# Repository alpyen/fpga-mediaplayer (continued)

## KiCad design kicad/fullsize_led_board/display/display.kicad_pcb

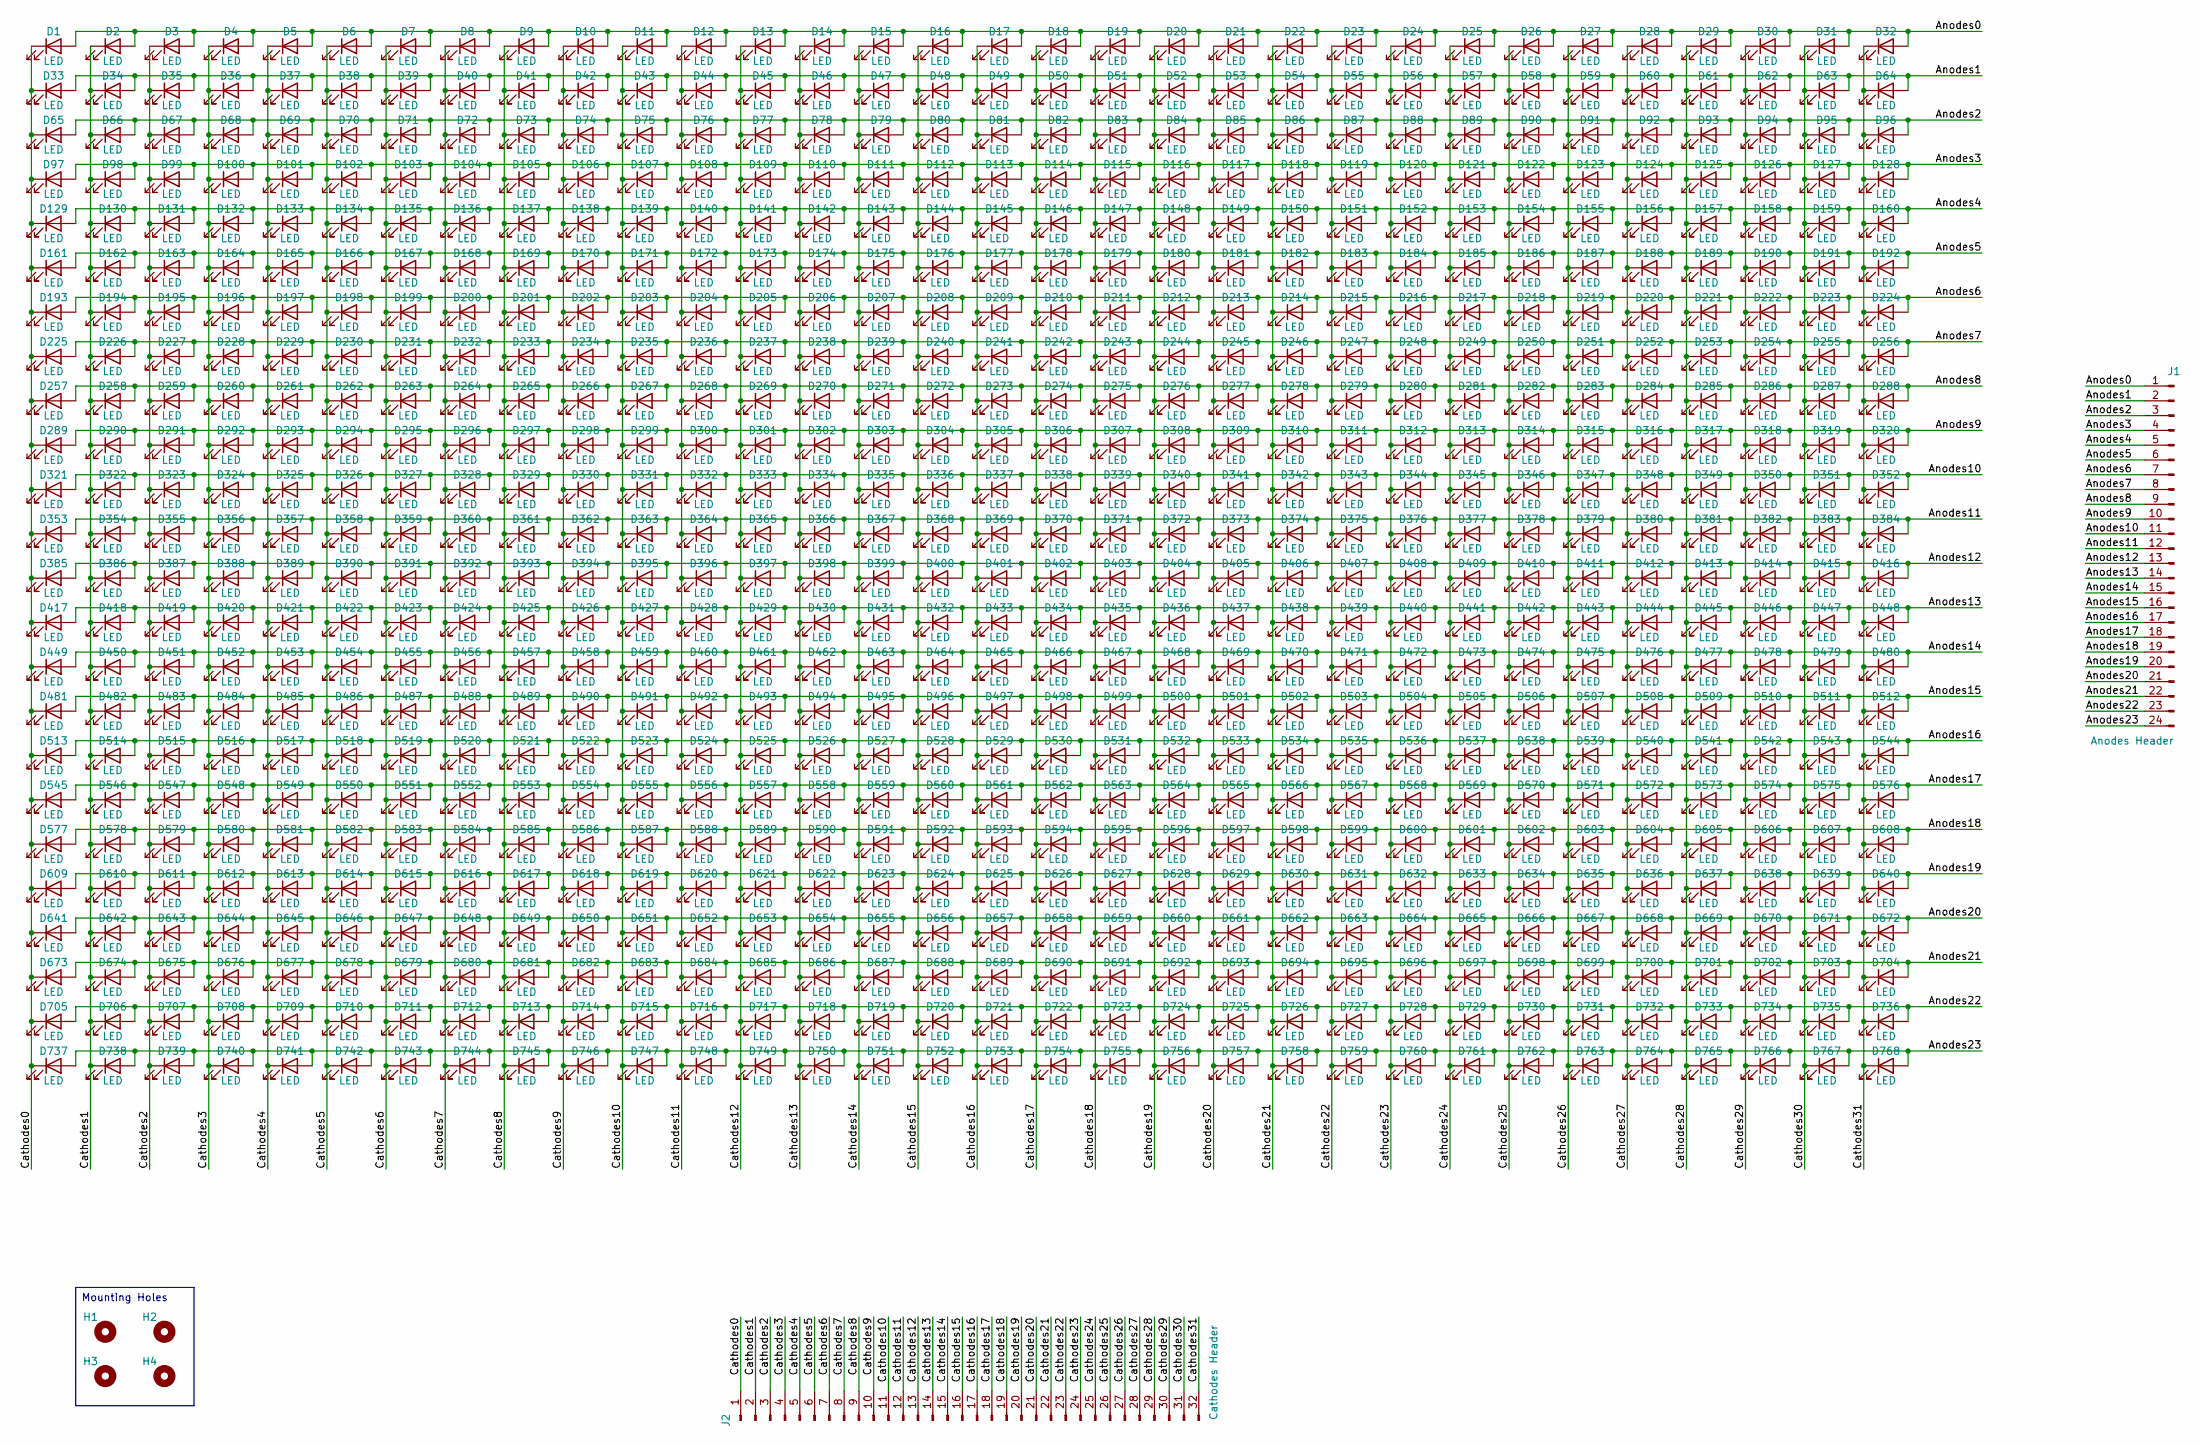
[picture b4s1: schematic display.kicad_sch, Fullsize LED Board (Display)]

Parts:
D1, D2, D3, D4, D5, D6, D7, D8, D9, D10, D11, D12, D13, D14, D15, D16, D17, D18, D19, D20, D21, D22, D23, D24, D25, D26, D27, D28, D29, D30, D31, D32, D33, D34, D35, D36, D37, D38, D39, D40, D41, D42, D43, D44, D45, D46, D47, D48, D49, D50, D51, D52, D53, D54, D55, D56, D57, D58, D59, D60, D61, D62, D63, D64, D65, D66, D67, D68, D69, D70, D71, D72, D73, D74, D75, D76, D77, D78, D79, D80, D81, D82, D83, D84, D85, D86, D87, D88, D89, D90, D91, D92, D93, D94, D95, D96, D97, D98, D99, D100, D101, D102, D103, D104, D105, D106, D107, D108, D109, D110, D111, D112, D113, D114, D115, D116, D117, D118, D119, D120, D121, D122, D123, D124, D125, D126, D127, D128, D129, D130, D131, D132, D133, D134, D135, D136, D137, D138, D139, D140, D141, D142, D143, D144, D145, D146, D147, D148, D149, D150, D151, D152, D153, D154, D155, D156, D157, D158, D159, D160, D161, D162, D163, D164, D165, D166, D167, D168, D169, D170, D171, D172, D173, D174, D175, D176, D177, D178, D179, D180, D181, D182, D183, D184, D185, D186, D187, D188, D189, D190, D191, D192, D193, D194, D195, D196, D197, D198, D199, D200, D201, D202, D203, D204, D205, D206, D207, D208, D209, D210, D211, D212, D213, D214, D215, D216, D217, D218, D219, D220, D221, D222, D223, D224, D225, D226, D227, D228, D229, D230, D231, D232, D233, D234, D235, D236, D237, D238, D239, D240, D241, D242, D243, D244, D245, D246, D247, D248, D249, D250, D251, D252, D253, D254, D255, D256, D257, D258, D259, D260, D261, D262, D263, D264, D265, D266, D267, D268, D269, D270, D271, D272, D273, D274, D275, D276, D277, D278, D279, D280, D281, D282, D283, D284, D285, D286, D287, D288, D289, D290, D291, D292, D293, D294, D295, D296, D297, D298, D299, D300, D301, D302, D303, D304, D305, D306, D307, D308, D309, D310, D311, D312, D313, D314, D315, D316, D317, D318, D319, D320, D321, D322, D323, D324, D325, D326, D327, D328, D329, D330, D331, D332, D333, D334, D335, D336, D337, D338, D339, D340, D341, D342, D343, D344, D345, D346, D347, D348, D349, D350, D351, D352, D353, D354, D355, D356, D357, D358, D359, D360, D361, D362, D363, D364, D365, D366, D367, D368, D369, D370, D371, D372, D373, D374, D375, D376, D377, D378, D379, D380, D381, D382, D383, D384, D385, D386, D387, D388, D389, D390, D391, D392, D393, D394, D395, D396, D397, D398, D399, D400, D401, D402, D403, D404, D405, D406, D407, D408, D409, D410, D411, D412, D413, D414, D415, D416, D417, D418, D419, D420, D421, D422, D423, D424, D425, D426, D427, D428, D429, D430, D431, D432, D433, D434, D435, D436, D437, D438, D439, D440, D441, D442, D443, D444, D445, D446, D447, D448, D449, D450, D451, D452, D453, D454, D455, D456, D457, D458, D459, D460, D461, D462, D463, D464, D465, D466, D467, D468, D469, D470, D471, D472, D473, D474, D475, D476, D477, D478, D479, D480, D481, D482, D483, D484, D485, D486, D487, D488, D489, D490, D491, D492, D493, D494, D495, D496, D497, D498, D499, D500, D501, D502, D503, D504, D505, D506, D507, D508, D509, D510, D511, D512, D513, D514, D515, D516, D517, D518, D519, D520, D521, D522, D523, D524, D525, D526, D527, D528, D529, D530, D531, D532, D533, D534, D535, D536, D537, D538, D539, D540, D541, D542, D543, D544, D545, D546, D547, D548, D549, D550, D551, D552, D553, D554, D555, D556, D557, D558, D559, D560, D561, D562, D563, D564, D565, D566, D567, D568, D569, D570, D571, D572, D573, D574, D575, D576, D577, D578, D579, D580, D581, D582, D583, D584, D585, D586, D587, D588, D589, D590, D591, D592, D593, D594, D595, D596, D597, D598, D599, D600, D601, D602, D603, D604, D605, D606, D607, D608, D609, D610, D611, D612, D613, D614, D615, D616, D617, D618, D619, D620, D621, D622, D623, D624, D625, D626, D627, D628, D629, D630, D631, D632, D633, D634, D635, D636, D637, D638, D639, D640, D641, D642, D643, D644, D645, D646, D647, D648, D649, D650, D651, D652, D653, D654, D655, D656, D657, D658, D659, D660, D661, D662, D663, D664, D665, D666, D667, D668, D669, D670, D671, D672, D673, D674, D675, D676, D677, D678, D679, D680, D681, D682, D683, D684, D685, D686, D687, D688, D689, D690, D691, D692, D693, D694, D695, D696, D697, D698, D699, D700, D701, D702, D703, D704, D705, D706, D707, D708, D709, D710, D711, D712, D713, D714, D715, D716, D717, D718, D719, D720, D721, D722, D723, D724, D725, D726, D727, D728, D729, D730, D731, D732, D733, D734, D735, D736, D737, D738, D739, D740, D741, D742, D743, D744, D745, D746, D747, D748, D749, D750, D751, D752, D753, D754, D755, D756, D757, D758, D759, D760, D761, D762, D763, D764, D765, D766, D767, D768: LED; LED_D5.0mm
H1, H2, H3, H4: MountingHole_3mm
J1: Anodes Header; PinHeader_1x24_P2.54mm_Vertical
J2: Cathodes Header; PinHeader_1x32_P2.54mm_Vertical

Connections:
/Anodes0: D1.2 (A), D2.2 (A), D3.2 (A), D4.2 (A), D5.2 (A), D6.2 (A), D7.2 (A), D8.2 (A), D9.2 (A), D10.2 (A), D11.2 (A), D12.2 (A), D13.2 (A), D14.2 (A), D15.2 (A), D16.2 (A), D17.2 (A), D18.2 (A), D19.2 (A), D20.2 (A), D21.2 (A), D22.2 (A), D23.2 (A), D24.2 (A), D25.2 (A), D26.2 (A), D27.2 (A), D28.2 (A), D29.2 (A), D30.2 (A), D31.2 (A), D32.2 (A), J1.1
/Anodes1: D33.2 (A), D34.2 (A), D35.2 (A), D36.2 (A), D37.2 (A), D38.2 (A), D39.2 (A), D40.2 (A), D41.2 (A), D42.2 (A), D43.2 (A), D44.2 (A), D45.2 (A), D46.2 (A), D47.2 (A), D48.2 (A), D49.2 (A), D50.2 (A), D51.2 (A), D52.2 (A), D53.2 (A), D54.2 (A), D55.2 (A), D56.2 (A), D57.2 (A), D58.2 (A), D59.2 (A), D60.2 (A), D61.2 (A), D62.2 (A), D63.2 (A), D64.2 (A), J1.2
/Anodes2: D65.2 (A), D66.2 (A), D67.2 (A), D68.2 (A), D69.2 (A), D70.2 (A), D71.2 (A), D72.2 (A), D73.2 (A), D74.2 (A), D75.2 (A), D76.2 (A), D77.2 (A), D78.2 (A), D79.2 (A), D80.2 (A), D81.2 (A), D82.2 (A), D83.2 (A), D84.2 (A), D85.2 (A), D86.2 (A), D87.2 (A), D88.2 (A), D89.2 (A), D90.2 (A), D91.2 (A), D92.2 (A), D93.2 (A), D94.2 (A), D95.2 (A), D96.2 (A), J1.3
/Anodes3: D97.2 (A), D98.2 (A), D99.2 (A), D100.2 (A), D101.2 (A), D102.2 (A), D103.2 (A), D104.2 (A), D105.2 (A), D106.2 (A), D107.2 (A), D108.2 (A), D109.2 (A), D110.2 (A), D111.2 (A), D112.2 (A), D113.2 (A), D114.2 (A), D115.2 (A), D116.2 (A), D117.2 (A), D118.2 (A), D119.2 (A), D120.2 (A), D121.2 (A), D122.2 (A), D123.2 (A), D124.2 (A), D125.2 (A), D126.2 (A), D127.2 (A), D128.2 (A), J1.4
/Anodes4: D129.2 (A), D130.2 (A), D131.2 (A), D132.2 (A), D133.2 (A), D134.2 (A), D135.2 (A), D136.2 (A), D137.2 (A), D138.2 (A), D139.2 (A), D140.2 (A), D141.2 (A), D142.2 (A), D143.2 (A), D144.2 (A), D145.2 (A), D146.2 (A), D147.2 (A), D148.2 (A), D149.2 (A), D150.2 (A), D151.2 (A), D152.2 (A), D153.2 (A), D154.2 (A), D155.2 (A), D156.2 (A), D157.2 (A), D158.2 (A), D159.2 (A), D160.2 (A), J1.5
/Anodes5: D161.2 (A), D162.2 (A), D163.2 (A), D164.2 (A), D165.2 (A), D166.2 (A), D167.2 (A), D168.2 (A), D169.2 (A), D170.2 (A), D171.2 (A), D172.2 (A), D173.2 (A), D174.2 (A), D175.2 (A), D176.2 (A), D177.2 (A), D178.2 (A), D179.2 (A), D180.2 (A), D181.2 (A), D182.2 (A), D183.2 (A), D184.2 (A), D185.2 (A), D186.2 (A), D187.2 (A), D188.2 (A), D189.2 (A), D190.2 (A), D191.2 (A), D192.2 (A), J1.6
/Anodes6: D193.2 (A), D194.2 (A), D195.2 (A), D196.2 (A), D197.2 (A), D198.2 (A), D199.2 (A), D200.2 (A), D201.2 (A), D202.2 (A), D203.2 (A), D204.2 (A), D205.2 (A), D206.2 (A), D207.2 (A), D208.2 (A), D209.2 (A), D210.2 (A), D211.2 (A), D212.2 (A), D213.2 (A), D214.2 (A), D215.2 (A), D216.2 (A), D217.2 (A), D218.2 (A), D219.2 (A), D220.2 (A), D221.2 (A), D222.2 (A), D223.2 (A), D224.2 (A), J1.7
/Anodes7: D225.2 (A), D226.2 (A), D227.2 (A), D228.2 (A), D229.2 (A), D230.2 (A), D231.2 (A), D232.2 (A), D233.2 (A), D234.2 (A), D235.2 (A), D236.2 (A), D237.2 (A), D238.2 (A), D239.2 (A), D240.2 (A), D241.2 (A), D242.2 (A), D243.2 (A), D244.2 (A), D245.2 (A), D246.2 (A), D247.2 (A), D248.2 (A), D249.2 (A), D250.2 (A), D251.2 (A), D252.2 (A), D253.2 (A), D254.2 (A), D255.2 (A), D256.2 (A), J1.8
/Anodes8: D257.2 (A), D258.2 (A), D259.2 (A), D260.2 (A), D261.2 (A), D262.2 (A), D263.2 (A), D264.2 (A), D265.2 (A), D266.2 (A), D267.2 (A), D268.2 (A), D269.2 (A), D270.2 (A), D271.2 (A), D272.2 (A), D273.2 (A), D274.2 (A), D275.2 (A), D276.2 (A), D277.2 (A), D278.2 (A), D279.2 (A), D280.2 (A), D281.2 (A), D282.2 (A), D283.2 (A), D284.2 (A), D285.2 (A), D286.2 (A), D287.2 (A), D288.2 (A), J1.9
/Anodes9: D289.2 (A), D290.2 (A), D291.2 (A), D292.2 (A), D293.2 (A), D294.2 (A), D295.2 (A), D296.2 (A), D297.2 (A), D298.2 (A), D299.2 (A), D300.2 (A), D301.2 (A), D302.2 (A), D303.2 (A), D304.2 (A), D305.2 (A), D306.2 (A), D307.2 (A), D308.2 (A), D309.2 (A), D310.2 (A), D311.2 (A), D312.2 (A), D313.2 (A), D314.2 (A), D315.2 (A), D316.2 (A), D317.2 (A), D318.2 (A), D319.2 (A), D320.2 (A), J1.10
/Anodes10: D321.2 (A), D322.2 (A), D323.2 (A), D324.2 (A), D325.2 (A), D326.2 (A), D327.2 (A), D328.2 (A), D329.2 (A), D330.2 (A), D331.2 (A), D332.2 (A), D333.2 (A), D334.2 (A), D335.2 (A), D336.2 (A), D337.2 (A), D338.2 (A), D339.2 (A), D340.2 (A), D341.2 (A), D342.2 (A), D343.2 (A), D344.2 (A), D345.2 (A), D346.2 (A), D347.2 (A), D348.2 (A), D349.2 (A), D350.2 (A), D351.2 (A), D352.2 (A), J1.11
/Anodes11: D353.2 (A), D354.2 (A), D355.2 (A), D356.2 (A), D357.2 (A), D358.2 (A), D359.2 (A), D360.2 (A), D361.2 (A), D362.2 (A), D363.2 (A), D364.2 (A), D365.2 (A), D366.2 (A), D367.2 (A), D368.2 (A), D369.2 (A), D370.2 (A), D371.2 (A), D372.2 (A), D373.2 (A), D374.2 (A), D375.2 (A), D376.2 (A), D377.2 (A), D378.2 (A), D379.2 (A), D380.2 (A), D381.2 (A), D382.2 (A), D383.2 (A), D384.2 (A), J1.12
/Anodes12: D385.2 (A), D386.2 (A), D387.2 (A), D388.2 (A), D389.2 (A), D390.2 (A), D391.2 (A), D392.2 (A), D393.2 (A), D394.2 (A), D395.2 (A), D396.2 (A), D397.2 (A), D398.2 (A), D399.2 (A), D400.2 (A), D401.2 (A), D402.2 (A), D403.2 (A), D404.2 (A), D405.2 (A), D406.2 (A), D407.2 (A), D408.2 (A), D409.2 (A), D410.2 (A), D411.2 (A), D412.2 (A), D413.2 (A), D414.2 (A), D415.2 (A), D416.2 (A), J1.13
/Anodes13: D417.2 (A), D418.2 (A), D419.2 (A), D420.2 (A), D421.2 (A), D422.2 (A), D423.2 (A), D424.2 (A), D425.2 (A), D426.2 (A), D427.2 (A), D428.2 (A), D429.2 (A), D430.2 (A), D431.2 (A), D432.2 (A), D433.2 (A), D434.2 (A), D435.2 (A), D436.2 (A), D437.2 (A), D438.2 (A), D439.2 (A), D440.2 (A), D441.2 (A), D442.2 (A), D443.2 (A), D444.2 (A), D445.2 (A), D446.2 (A), D447.2 (A), D448.2 (A), J1.14
/Anodes14: D449.2 (A), D450.2 (A), D451.2 (A), D452.2 (A), D453.2 (A), D454.2 (A), D455.2 (A), D456.2 (A), D457.2 (A), D458.2 (A), D459.2 (A), D460.2 (A), D461.2 (A), D462.2 (A), D463.2 (A), D464.2 (A), D465.2 (A), D466.2 (A), D467.2 (A), D468.2 (A), D469.2 (A), D470.2 (A), D471.2 (A), D472.2 (A), D473.2 (A), D474.2 (A), D475.2 (A), D476.2 (A), D477.2 (A), D478.2 (A), D479.2 (A), D480.2 (A), J1.15
/Anodes15: D481.2 (A), D482.2 (A), D483.2 (A), D484.2 (A), D485.2 (A), D486.2 (A), D487.2 (A), D488.2 (A), D489.2 (A), D490.2 (A), D491.2 (A), D492.2 (A), D493.2 (A), D494.2 (A), D495.2 (A), D496.2 (A), D497.2 (A), D498.2 (A), D499.2 (A), D500.2 (A), D501.2 (A), D502.2 (A), D503.2 (A), D504.2 (A), D505.2 (A), D506.2 (A), D507.2 (A), D508.2 (A), D509.2 (A), D510.2 (A), D511.2 (A), D512.2 (A), J1.16
/Anodes16: D513.2 (A), D514.2 (A), D515.2 (A), D516.2 (A), D517.2 (A), D518.2 (A), D519.2 (A), D520.2 (A), D521.2 (A), D522.2 (A), D523.2 (A), D524.2 (A), D525.2 (A), D526.2 (A), D527.2 (A), D528.2 (A), D529.2 (A), D530.2 (A), D531.2 (A), D532.2 (A), D533.2 (A), D534.2 (A), D535.2 (A), D536.2 (A), D537.2 (A), D538.2 (A), D539.2 (A), D540.2 (A), D541.2 (A), D542.2 (A), D543.2 (A), D544.2 (A), J1.17
/Anodes17: D545.2 (A), D546.2 (A), D547.2 (A), D548.2 (A), D549.2 (A), D550.2 (A), D551.2 (A), D552.2 (A), D553.2 (A), D554.2 (A), D555.2 (A), D556.2 (A), D557.2 (A), D558.2 (A), D559.2 (A), D560.2 (A), D561.2 (A), D562.2 (A), D563.2 (A), D564.2 (A), D565.2 (A), D566.2 (A), D567.2 (A), D568.2 (A), D569.2 (A), D570.2 (A), D571.2 (A), D572.2 (A), D573.2 (A), D574.2 (A), D575.2 (A), D576.2 (A), J1.18
/Anodes18: D577.2 (A), D578.2 (A), D579.2 (A), D580.2 (A), D581.2 (A), D582.2 (A), D583.2 (A), D584.2 (A), D585.2 (A), D586.2 (A), D587.2 (A), D588.2 (A), D589.2 (A), D590.2 (A), D591.2 (A), D592.2 (A), D593.2 (A), D594.2 (A), D595.2 (A), D596.2 (A), D597.2 (A), D598.2 (A), D599.2 (A), D600.2 (A), D601.2 (A), D602.2 (A), D603.2 (A), D604.2 (A), D605.2 (A), D606.2 (A), D607.2 (A), D608.2 (A), J1.19
/Anodes19: D609.2 (A), D610.2 (A), D611.2 (A), D612.2 (A), D613.2 (A), D614.2 (A), D615.2 (A), D616.2 (A), D617.2 (A), D618.2 (A), D619.2 (A), D620.2 (A), D621.2 (A), D622.2 (A), D623.2 (A), D624.2 (A), D625.2 (A), D626.2 (A), D627.2 (A), D628.2 (A), D629.2 (A), D630.2 (A), D631.2 (A), D632.2 (A), D633.2 (A), D634.2 (A), D635.2 (A), D636.2 (A), D637.2 (A), D638.2 (A), D639.2 (A), D640.2 (A), J1.20
/Anodes20: D641.2 (A), D642.2 (A), D643.2 (A), D644.2 (A), D645.2 (A), D646.2 (A), D647.2 (A), D648.2 (A), D649.2 (A), D650.2 (A), D651.2 (A), D652.2 (A), D653.2 (A), D654.2 (A), D655.2 (A), D656.2 (A), D657.2 (A), D658.2 (A), D659.2 (A), D660.2 (A), D661.2 (A), D662.2 (A), D663.2 (A), D664.2 (A), D665.2 (A), D666.2 (A), D667.2 (A), D668.2 (A), D669.2 (A), D670.2 (A), D671.2 (A), D672.2 (A), J1.21
/Anodes21: D673.2 (A), D674.2 (A), D675.2 (A), D676.2 (A), D677.2 (A), D678.2 (A), D679.2 (A), D680.2 (A), D681.2 (A), D682.2 (A), D683.2 (A), D684.2 (A), D685.2 (A), D686.2 (A), D687.2 (A), D688.2 (A), D689.2 (A), D690.2 (A), D691.2 (A), D692.2 (A), D693.2 (A), D694.2 (A), D695.2 (A), D696.2 (A), D697.2 (A), D698.2 (A), D699.2 (A), D700.2 (A), D701.2 (A), D702.2 (A), D703.2 (A), D704.2 (A), J1.22
/Anodes22: D705.2 (A), D706.2 (A), D707.2 (A), D708.2 (A), D709.2 (A), D710.2 (A), D711.2 (A), D712.2 (A), D713.2 (A), D714.2 (A), D715.2 (A), D716.2 (A), D717.2 (A), D718.2 (A), D719.2 (A), D720.2 (A), D721.2 (A), D722.2 (A), D723.2 (A), D724.2 (A), D725.2 (A), D726.2 (A), D727.2 (A), D728.2 (A), D729.2 (A), D730.2 (A), D731.2 (A), D732.2 (A), D733.2 (A), D734.2 (A), D735.2 (A), D736.2 (A), J1.23
/Anodes23: D737.2 (A), D738.2 (A), D739.2 (A), D740.2 (A), D741.2 (A), D742.2 (A), D743.2 (A), D744.2 (A), D745.2 (A), D746.2 (A), D747.2 (A), D748.2 (A), D749.2 (A), D750.2 (A), D751.2 (A), D752.2 (A), D753.2 (A), D754.2 (A), D755.2 (A), D756.2 (A), D757.2 (A), D758.2 (A), D759.2 (A), D760.2 (A), D761.2 (A), D762.2 (A), D763.2 (A), D764.2 (A), D765.2 (A), D766.2 (A), D767.2 (A), D768.2 (A), J1.24
/Cathodes0: D1.1 (K), D33.1 (K), D65.1 (K), D97.1 (K), D129.1 (K), D161.1 (K), D193.1 (K), D225.1 (K), D257.1 (K), D289.1 (K), D321.1 (K), D353.1 (K), D385.1 (K), D417.1 (K), D449.1 (K), D481.1 (K), D513.1 (K), D545.1 (K), D577.1 (K), D609.1 (K), D641.1 (K), D673.1 (K), D705.1 (K), D737.1 (K), J2.1
/Cathodes1: D2.1 (K), D34.1 (K), D66.1 (K), D98.1 (K), D130.1 (K), D162.1 (K), D194.1 (K), D226.1 (K), D258.1 (K), D290.1 (K), D322.1 (K), D354.1 (K), D386.1 (K), D418.1 (K), D450.1 (K), D482.1 (K), D514.1 (K), D546.1 (K), D578.1 (K), D610.1 (K), D642.1 (K), D674.1 (K), D706.1 (K), D738.1 (K), J2.2
/Cathodes2: D3.1 (K), D35.1 (K), D67.1 (K), D99.1 (K), D131.1 (K), D163.1 (K), D195.1 (K), D227.1 (K), D259.1 (K), D291.1 (K), D323.1 (K), D355.1 (K), D387.1 (K), D419.1 (K), D451.1 (K), D483.1 (K), D515.1 (K), D547.1 (K), D579.1 (K), D611.1 (K), D643.1 (K), D675.1 (K), D707.1 (K), D739.1 (K), J2.3
/Cathodes3: D4.1 (K), D36.1 (K), D68.1 (K), D100.1 (K), D132.1 (K), D164.1 (K), D196.1 (K), D228.1 (K), D260.1 (K), D292.1 (K), D324.1 (K), D356.1 (K), D388.1 (K), D420.1 (K), D452.1 (K), D484.1 (K), D516.1 (K), D548.1 (K), D580.1 (K), D612.1 (K), D644.1 (K), D676.1 (K), D708.1 (K), D740.1 (K), J2.4
/Cathodes4: D5.1 (K), D37.1 (K), D69.1 (K), D101.1 (K), D133.1 (K), D165.1 (K), D197.1 (K), D229.1 (K), D261.1 (K), D293.1 (K), D325.1 (K), D357.1 (K), D389.1 (K), D421.1 (K), D453.1 (K), D485.1 (K), D517.1 (K), D549.1 (K), D581.1 (K), D613.1 (K), D645.1 (K), D677.1 (K), D709.1 (K), D741.1 (K), J2.5
/Cathodes5: D6.1 (K), D38.1 (K), D70.1 (K), D102.1 (K), D134.1 (K), D166.1 (K), D198.1 (K), D230.1 (K), D262.1 (K), D294.1 (K), D326.1 (K), D358.1 (K), D390.1 (K), D422.1 (K), D454.1 (K), D486.1 (K), D518.1 (K), D550.1 (K), D582.1 (K), D614.1 (K), D646.1 (K), D678.1 (K), D710.1 (K), D742.1 (K), J2.6
/Cathodes6: D7.1 (K), D39.1 (K), D71.1 (K), D103.1 (K), D135.1 (K), D167.1 (K), D199.1 (K), D231.1 (K), D263.1 (K), D295.1 (K), D327.1 (K), D359.1 (K), D391.1 (K), D423.1 (K), D455.1 (K), D487.1 (K), D519.1 (K), D551.1 (K), D583.1 (K), D615.1 (K), D647.1 (K), D679.1 (K), D711.1 (K), D743.1 (K), J2.7
/Cathodes7: D8.1 (K), D40.1 (K), D72.1 (K), D104.1 (K), D136.1 (K), D168.1 (K), D200.1 (K), D232.1 (K), D264.1 (K), D296.1 (K), D328.1 (K), D360.1 (K), D392.1 (K), D424.1 (K), D456.1 (K), D488.1 (K), D520.1 (K), D552.1 (K), D584.1 (K), D616.1 (K), D648.1 (K), D680.1 (K), D712.1 (K), D744.1 (K), J2.8
/Cathodes8: D9.1 (K), D41.1 (K), D73.1 (K), D105.1 (K), D137.1 (K), D169.1 (K), D201.1 (K), D233.1 (K), D265.1 (K), D297.1 (K), D329.1 (K), D361.1 (K), D393.1 (K), D425.1 (K), D457.1 (K), D489.1 (K), D521.1 (K), D553.1 (K), D585.1 (K), D617.1 (K), D649.1 (K), D681.1 (K), D713.1 (K), D745.1 (K), J2.9
/Cathodes9: D10.1 (K), D42.1 (K), D74.1 (K), D106.1 (K), D138.1 (K), D170.1 (K), D202.1 (K), D234.1 (K), D266.1 (K), D298.1 (K), D330.1 (K), D362.1 (K), D394.1 (K), D426.1 (K), D458.1 (K), D490.1 (K), D522.1 (K), D554.1 (K), D586.1 (K), D618.1 (K), D650.1 (K), D682.1 (K), D714.1 (K), D746.1 (K), J2.10
/Cathodes10: D11.1 (K), D43.1 (K), D75.1 (K), D107.1 (K), D139.1 (K), D171.1 (K), D203.1 (K), D235.1 (K), D267.1 (K), D299.1 (K), D331.1 (K), D363.1 (K), D395.1 (K), D427.1 (K), D459.1 (K), D491.1 (K), D523.1 (K), D555.1 (K), D587.1 (K), D619.1 (K), D651.1 (K), D683.1 (K), D715.1 (K), D747.1 (K), J2.11
/Cathodes11: D12.1 (K), D44.1 (K), D76.1 (K), D108.1 (K), D140.1 (K), D172.1 (K), D204.1 (K), D236.1 (K), D268.1 (K), D300.1 (K), D332.1 (K), D364.1 (K), D396.1 (K), D428.1 (K), D460.1 (K), D492.1 (K), D524.1 (K), D556.1 (K), D588.1 (K), D620.1 (K), D652.1 (K), D684.1 (K), D716.1 (K), D748.1 (K), J2.12
/Cathodes12: D13.1 (K), D45.1 (K), D77.1 (K), D109.1 (K), D141.1 (K), D173.1 (K), D205.1 (K), D237.1 (K), D269.1 (K), D301.1 (K), D333.1 (K), D365.1 (K), D397.1 (K), D429.1 (K), D461.1 (K), D493.1 (K), D525.1 (K), D557.1 (K), D589.1 (K), D621.1 (K), D653.1 (K), D685.1 (K), D717.1 (K), D749.1 (K), J2.13
/Cathodes13: D14.1 (K), D46.1 (K), D78.1 (K), D110.1 (K), D142.1 (K), D174.1 (K), D206.1 (K), D238.1 (K), D270.1 (K), D302.1 (K), D334.1 (K), D366.1 (K), D398.1 (K), D430.1 (K), D462.1 (K), D494.1 (K), D526.1 (K), D558.1 (K), D590.1 (K), D622.1 (K), D654.1 (K), D686.1 (K), D718.1 (K), D750.1 (K), J2.14
/Cathodes14: D15.1 (K), D47.1 (K), D79.1 (K), D111.1 (K), D143.1 (K), D175.1 (K), D207.1 (K), D239.1 (K), D271.1 (K), D303.1 (K), D335.1 (K), D367.1 (K), D399.1 (K), D431.1 (K), D463.1 (K), D495.1 (K), D527.1 (K), D559.1 (K), D591.1 (K), D623.1 (K), D655.1 (K), D687.1 (K), D719.1 (K), D751.1 (K), J2.15
/Cathodes15: D16.1 (K), D48.1 (K), D80.1 (K), D112.1 (K), D144.1 (K), D176.1 (K), D208.1 (K), D240.1 (K), D272.1 (K), D304.1 (K), D336.1 (K), D368.1 (K), D400.1 (K), D432.1 (K), D464.1 (K), D496.1 (K), D528.1 (K), D560.1 (K), D592.1 (K), D624.1 (K), D656.1 (K), D688.1 (K), D720.1 (K), D752.1 (K), J2.16
/Cathodes16: D17.1 (K), D49.1 (K), D81.1 (K), D113.1 (K), D145.1 (K), D177.1 (K), D209.1 (K), D241.1 (K), D273.1 (K), D305.1 (K), D337.1 (K), D369.1 (K), D401.1 (K), D433.1 (K), D465.1 (K), D497.1 (K), D529.1 (K), D561.1 (K), D593.1 (K), D625.1 (K), D657.1 (K), D689.1 (K), D721.1 (K), D753.1 (K), J2.17
/Cathodes17: D18.1 (K), D50.1 (K), D82.1 (K), D114.1 (K), D146.1 (K), D178.1 (K), D210.1 (K), D242.1 (K), D274.1 (K), D306.1 (K), D338.1 (K), D370.1 (K), D402.1 (K), D434.1 (K), D466.1 (K), D498.1 (K), D530.1 (K), D562.1 (K), D594.1 (K), D626.1 (K), D658.1 (K), D690.1 (K), D722.1 (K), D754.1 (K), J2.18
/Cathodes18: D19.1 (K), D51.1 (K), D83.1 (K), D115.1 (K), D147.1 (K), D179.1 (K), D211.1 (K), D243.1 (K), D275.1 (K), D307.1 (K), D339.1 (K), D371.1 (K), D403.1 (K), D435.1 (K), D467.1 (K), D499.1 (K), D531.1 (K), D563.1 (K), D595.1 (K), D627.1 (K), D659.1 (K), D691.1 (K), D723.1 (K), D755.1 (K), J2.19
/Cathodes19: D20.1 (K), D52.1 (K), D84.1 (K), D116.1 (K), D148.1 (K), D180.1 (K), D212.1 (K), D244.1 (K), D276.1 (K), D308.1 (K), D340.1 (K), D372.1 (K), D404.1 (K), D436.1 (K), D468.1 (K), D500.1 (K), D532.1 (K), D564.1 (K), D596.1 (K), D628.1 (K), D660.1 (K), D692.1 (K), D724.1 (K), D756.1 (K), J2.20
/Cathodes20: D21.1 (K), D53.1 (K), D85.1 (K), D117.1 (K), D149.1 (K), D181.1 (K), D213.1 (K), D245.1 (K), D277.1 (K), D309.1 (K), D341.1 (K), D373.1 (K), D405.1 (K), D437.1 (K), D469.1 (K), D501.1 (K), D533.1 (K), D565.1 (K), D597.1 (K), D629.1 (K), D661.1 (K), D693.1 (K), D725.1 (K), D757.1 (K), J2.21
/Cathodes21: D22.1 (K), D54.1 (K), D86.1 (K), D118.1 (K), D150.1 (K), D182.1 (K), D214.1 (K), D246.1 (K), D278.1 (K), D310.1 (K), D342.1 (K), D374.1 (K), D406.1 (K), D438.1 (K), D470.1 (K), D502.1 (K), D534.1 (K), D566.1 (K), D598.1 (K), D630.1 (K), D662.1 (K), D694.1 (K), D726.1 (K), D758.1 (K), J2.22
/Cathodes22: D23.1 (K), D55.1 (K), D87.1 (K), D119.1 (K), D151.1 (K), D183.1 (K), D215.1 (K), D247.1 (K), D279.1 (K), D311.1 (K), D343.1 (K), D375.1 (K), D407.1 (K), D439.1 (K), D471.1 (K), D503.1 (K), D535.1 (K), D567.1 (K), D599.1 (K), D631.1 (K), D663.1 (K), D695.1 (K), D727.1 (K), D759.1 (K), J2.23
/Cathodes23: D24.1 (K), D56.1 (K), D88.1 (K), D120.1 (K), D152.1 (K), D184.1 (K), D216.1 (K), D248.1 (K), D280.1 (K), D312.1 (K), D344.1 (K), D376.1 (K), D408.1 (K), D440.1 (K), D472.1 (K), D504.1 (K), D536.1 (K), D568.1 (K), D600.1 (K), D632.1 (K), D664.1 (K), D696.1 (K), D728.1 (K), D760.1 (K), J2.24
/Cathodes24: D25.1 (K), D57.1 (K), D89.1 (K), D121.1 (K), D153.1 (K), D185.1 (K), D217.1 (K), D249.1 (K), D281.1 (K), D313.1 (K), D345.1 (K), D377.1 (K), D409.1 (K), D441.1 (K), D473.1 (K), D505.1 (K), D537.1 (K), D569.1 (K), D601.1 (K), D633.1 (K), D665.1 (K), D697.1 (K), D729.1 (K), D761.1 (K), J2.25
/Cathodes25: D26.1 (K), D58.1 (K), D90.1 (K), D122.1 (K), D154.1 (K), D186.1 (K), D218.1 (K), D250.1 (K), D282.1 (K), D314.1 (K), D346.1 (K), D378.1 (K), D410.1 (K), D442.1 (K), D474.1 (K), D506.1 (K), D538.1 (K), D570.1 (K), D602.1 (K), D634.1 (K), D666.1 (K), D698.1 (K), D730.1 (K), D762.1 (K), J2.26
/Cathodes26: D27.1 (K), D59.1 (K), D91.1 (K), D123.1 (K), D155.1 (K), D187.1 (K), D219.1 (K), D251.1 (K), D283.1 (K), D315.1 (K), D347.1 (K), D379.1 (K), D411.1 (K), D443.1 (K), D475.1 (K), D507.1 (K), D539.1 (K), D571.1 (K), D603.1 (K), D635.1 (K), D667.1 (K), D699.1 (K), D731.1 (K), D763.1 (K), J2.27
/Cathodes27: D28.1 (K), D60.1 (K), D92.1 (K), D124.1 (K), D156.1 (K), D188.1 (K), D220.1 (K), D252.1 (K), D284.1 (K), D316.1 (K), D348.1 (K), D380.1 (K), D412.1 (K), D444.1 (K), D476.1 (K), D508.1 (K), D540.1 (K), D572.1 (K), D604.1 (K), D636.1 (K), D668.1 (K), D700.1 (K), D732.1 (K), D764.1 (K), J2.28
/Cathodes28: D29.1 (K), D61.1 (K), D93.1 (K), D125.1 (K), D157.1 (K), D189.1 (K), D221.1 (K), D253.1 (K), D285.1 (K), D317.1 (K), D349.1 (K), D381.1 (K), D413.1 (K), D445.1 (K), D477.1 (K), D509.1 (K), D541.1 (K), D573.1 (K), D605.1 (K), D637.1 (K), D669.1 (K), D701.1 (K), D733.1 (K), D765.1 (K), J2.29
/Cathodes29: D30.1 (K), D62.1 (K), D94.1 (K), D126.1 (K), D158.1 (K), D190.1 (K), D222.1 (K), D254.1 (K), D286.1 (K), D318.1 (K), D350.1 (K), D382.1 (K), D414.1 (K), D446.1 (K), D478.1 (K), D510.1 (K), D542.1 (K), D574.1 (K), D606.1 (K), D638.1 (K), D670.1 (K), D702.1 (K), D734.1 (K), D766.1 (K), J2.30
/Cathodes30: D31.1 (K), D63.1 (K), D95.1 (K), D127.1 (K), D159.1 (K), D191.1 (K), D223.1 (K), D255.1 (K), D287.1 (K), D319.1 (K), D351.1 (K), D383.1 (K), D415.1 (K), D447.1 (K), D479.1 (K), D511.1 (K), D543.1 (K), D575.1 (K), D607.1 (K), D639.1 (K), D671.1 (K), D703.1 (K), D735.1 (K), D767.1 (K), J2.31
/Cathodes31: D32.1 (K), D64.1 (K), D96.1 (K), D128.1 (K), D160.1 (K), D192.1 (K), D224.1 (K), D256.1 (K), D288.1 (K), D320.1 (K), D352.1 (K), D384.1 (K), D416.1 (K), D448.1 (K), D480.1 (K), D512.1 (K), D544.1 (K), D576.1 (K), D608.1 (K), D640.1 (K), D672.1 (K), D704.1 (K), D736.1 (K), D768.1 (K), J2.32

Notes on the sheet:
Mounting Holes

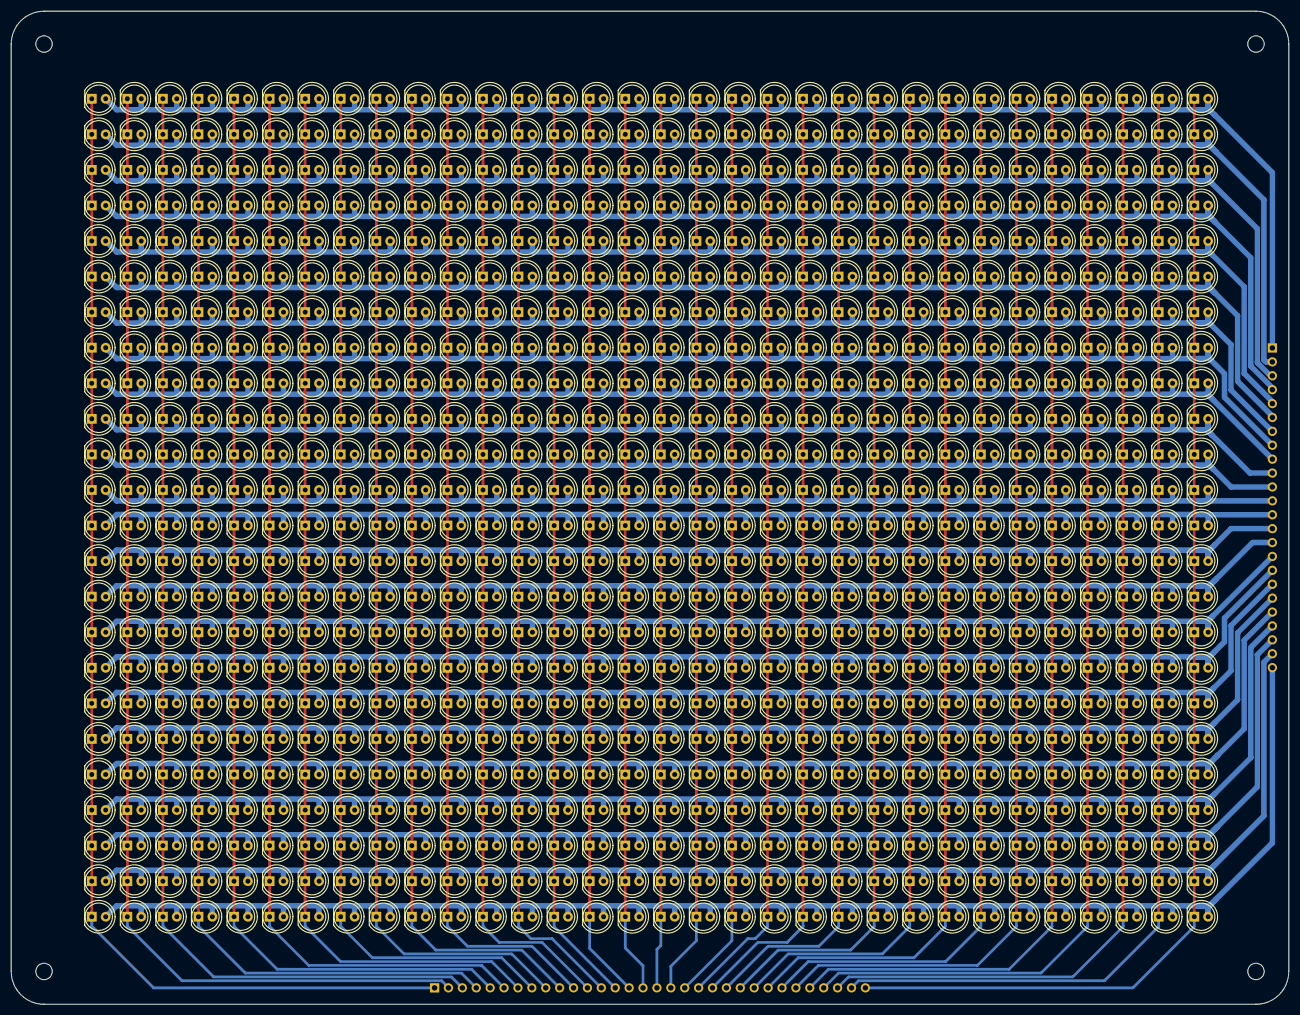
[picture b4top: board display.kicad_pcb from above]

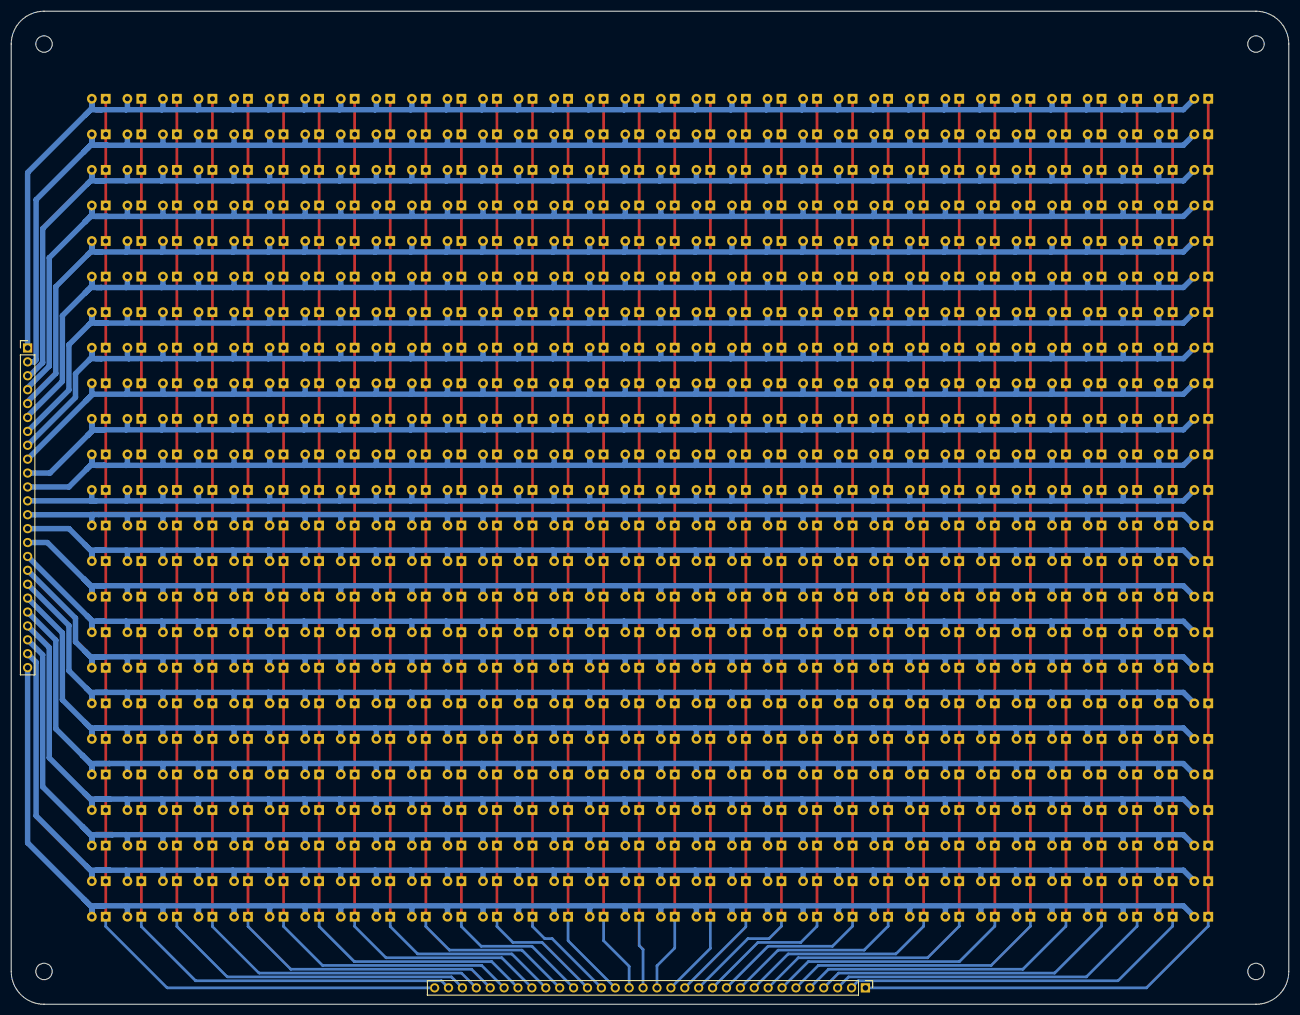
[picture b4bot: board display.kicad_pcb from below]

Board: 2 copper layers, 233.5 x 181.5 mm, 774 parts (2 on the bottom side), 56 nets.
